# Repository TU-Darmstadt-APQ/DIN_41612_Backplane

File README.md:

# 19″ IEC 60603-2 (DIN 41612) Backplane
This repository contains the [KiCad](https://www.kicad.org/) schematics and design files for a 19″ backplane designed according to [IEEE 1101.1-1998](https://ieeexplore.ieee.org/document/741932) to mount the laser electronics in the [Eurocard](https://en.wikipedia.org/wiki/Eurocard_(printed_circuit_board)) form factor developed by APQ. See [below](#introduction) for a list of compatible devices. The design files can be found on the [releases](../../releases) page.

## Contents
- [Introduction](#introduction)
- [Datasheet](#datasheet)
- [Installation](#installation)
- [Design Files](#design-files)
- [Related Repositories](#related-repositories)
- [Versioning](#versioning)
- [License](#license)

## Introduction
This repository contains the schematics for the APQ 19″ sub-rack backplanes to mount electronics within a 19″ rack. The backplanes use several [IEC 60603-2](https://en.wikipedia.org/wiki/DIN_41612) C64AC connectors that can be configured to mount several different types of [Eurocard](https://en.wikipedia.org/wiki/Eurocard_(printed_circuit_board)) devices used by this group.  There is space for up to 6 connectors mountable in different positions to accommodate both the [Fischer Elektronik HB ME 14](https://www.fischerelektronik.com/web_fischer/en_GB/cases/N06.011/19%22%20insert%20modules/$catalogue/fischerData/PR/HBME14_/index.xhtml) and the [Fischer Elektronik TFP 3 14](https://www.fischerelektronik.com/web_fischer/en_GB/cases/N06.05/Part%20front%20panels/$catalogue/fischerData/PR/TFP14/index.xhtml) system.

Compatible devices can be found here:
- [Digital Controller for Laser Frequency Stabilization](https://github.com/TU-Darmstadt-APQ/RedPitaya-Lockbox) (RedPitaya-Lockbox)
- [Digital Controller for Laser Intensity Stabilization](https://github.com/TU-Darmstadt-APQ/RedPitaya-IntStab) (RedPitaya-IntStab)
- [Ultra Low Noise Diode Laser Driver](https://github.com/TU-Darmstadt-APQ/DgDrive) (DgDrive)
- [Phase-Frequency Detector](https://github.com/TU-Darmstadt-APQ/phase-frequency_detector)
- [Modulation Transfer Spectroscopy (MTS) Module](https://github.com/TU-Darmstadt-APQ/MTS_module)
- [Multi-purpose OpAmp Circuit Board](https://github.com/TU-Darmstadt-APQ/Multi-purpose_OpAmp_Circuit)
- [PDH Module](https://github.com/TU-Darmstadt-APQ/PDH-module)

## Datasheet
There is a datasheet available that lists the most important electrical and mechanical specifications. The latest version can be found [here](../../releases/latest/download/datasheet.pdf). Older version can be found attached to the respective [release](../../releases).

## Installation
The backplane is designed to be mounted inside a 19″ sub-rack chassis.  The most common systems used in this group are the [Schroff EuropacPRO](https://schroff.nvent.com/de-de/products/enc24563-142) and the [Fischer Elektronik BGT 384 180](https://www.fischerelektronik.de/web_fischer/en_GB/cases/N05.1/19%22%20subracks/$catalogue/fischerData/PR/BGT384_180/search.xhtml). Additionally a power supply must be provided. Typically, a rack mountable DC power supply like an [HP 6632B](https://www.keysight.com/us/en/product/6632B/100-watt-system-power-supply-20v-5a.html) is used for each rail.

### Required components and tools
- [ ] Torque screwdriver of size TX8, set to 0.3 Nm
- [ ] 1.3 mm screwdriver for hexagonal socket screws
- [ ] [3 U](https://en.wikipedia.org/wiki/Rack_unit) 19″ sub-rack chassis
  - [Schroff EuropacPRO](https://schroff.nvent.com/de-de/products/enc24563-142) or
  - [Fischer Elektronik BGT 384 180](https://www.fischerelektronik.de/web_fischer/en_GB/cases/N05.1/19%22%20subracks/$catalogue/fischerData/PR/BGT384_180/search.xhtml)) and the following accessories:
    - 2x [Fischer Elektronik IST 84](https://www.fischerelektronik.de/web_fischer/en_GB/cases/N05.2/Accessories%20for%2019%22%20subracks/$catalogue/fischerData/PG/BGT_IST84/search.xhtml) 3 mm isolation strips. These go between the chassis and the backplane.
    - 1x [Fischer Elektronik BGT 384/2](https://www.fischerelektronik.de/web_fischer/en_GB/cases/N06.09/Mounting%20accessories/$catalogue/fischerData/PR/BGT384_2M2.5/index.xhtml) M2.5 mounting strips. A package contains for strips, two for each side of the chassis.
    - 6x [Fischer Elektronik FSC 160](https://www.fischerelektronik.de/web_fischer/en_GB/cases/N05.2/Accessories%20for%2019%22%20subracks/$catalogue/fischerData/PR/FSC160/index.xhtml), one for each module installed.
    - 1x optional [Fischer Elektronik AB211](https://www.fischerelektronik.com/web_fischer/en_GB/cases/N05.2/Accessories%20for%2019%22%20subracks/$catalogue/fischerData/PR/AB211/search.xhtml) cover panel. These can be made of mild steel on special order for additional magnetic shielding compared to aluminium.
- [ ] Power supply with ±15 V outputs
- [ ] Power cable with a  [MSTB 2,5 HC/ 3-ST-5,08](https://www.phoenixcontact.com/en-us/products/pcb-plug-mstb-25-hc-3-st-508-1911978). See [power cable assembly](#power-cable-assembly) below for details.
- [ ] Up to 6  female straight [IEC 60603-2](https://en.wikipedia.org/wiki/DIN_41612)  C64AC connectors depending on the number of devices to be installed. Use class 1 or 2 connectors for better longevity. Examples are [ept 304-40054-01](https://www.ept-connectors.com/index.php?304-40054-01_en) via [Farnell](https://de.farnell.com/ept/304-40054-01/steckv-din-41612-buchsenleist/dp/2758954?st=304-40054-01) or [Harting 09032646824](https://b2b.harting.com/ebusiness/de/DIN-Signal-C064FS-29C1-2/09032646824) via [RS](https://de.rs-online.com/web/p/din-41612-steckverbinder/9235025) or [Mouser](https://eu.mouser.com/ProductDetail/HARTING/09032646824?qs=gIpPgrDBK%2FjuvkAKv%252BIFBQ%3D%3D).
- [ ] 8x M2.5x8 DIN 914 / ISO 4027 set screws to fasten the  [Fischer Elektronik BGT 384/2](https://www.fischerelektronik.de/web_fischer/en_GB/cases/N06.09/Mounting%20accessories/$catalogue/fischerData/PR/BGT384_2M2.5/index.xhtml) mounting strips
 - [ ] 10x M2.5x10 ISO 14583 TX8 screws
 - [ ] 10x M2.5 DIN 125-A / ISO 7089 plain washers

### Installation steps
> [!IMPORTANT]
> Use a torque screwdriver (0.3 Nm) to tighten the screws holding the PCB, otherwise the PCB might flex and damage components.

- Start by soldering in the [IEC 60603-2](https://en.wikipedia.org/wiki/DIN_41612) connectors. There are markings on the PCB that show where to install these depending on the type of device enclosure used. Devices built around [Fischer Elektronik HB ME 14](https://www.fischerelektronik.com/web_fischer/en_GB/cases/N06.011/19%22%20insert%20modules/$catalogue/fischerData/PR/HBME14_/index.xhtml) and [Fischer Elektronik TFP 3 14](https://www.fischerelektronik.com/web_fischer/en_GB/cases/N06.05/Part%20front%20panels/$catalogue/fischerData/PR/TFP14/index.xhtml) are supported.
- The backplane must be fixed to the subrack assembly by 5 equidistant M2.5x10 mm TX8 screws installed in each of the top and bottom row of mounting holes. Use the torque screwdriver set to 0.3 Nm to fasten the screws. Do not use a higher torque or the PCB might flex and damage the SMD ceramic capacitors. Do also remember to put the [Fischer Elektronik IST 84](https://www.fischerelektronik.de/web_fischer/en_GB/cases/N05.2/Accessories%20for%2019%22%20subracks/$catalogue/fischerData/PG/BGT_IST84/search.xhtml) 3 mm isolation strips between the backplane and the subrack if using a Fischer rack. Similar strips come with the  [Schroff EuropacPRO](https://schroff.nvent.com/de-de/products/enc24563-142) subracks as well. Otherwise the [Eurocard](https://en.wikipedia.org/wiki/Eurocard_(printed_circuit_board)) modules will not fit.
- Once firmly installed, connect the [power cable](power-cable-assembly) to the PCB and the power supply and set the the power supply to ±15 V without any devices inserted into the sub-rack. When the power supply is turned on, two green LEDs should light up to signal that the input voltage is of correct polarity and value.
- Turn off the power supply and insert the devices.

### Power cable assembly
The board has a [MSTBA 2,5 HC/ 3-G-5,08](https://www.phoenixcontact.com/en-us/products/pcb-header-mstba-25-hc-3-g-508-1923872) header. The plug required on the cable side is a [MSTB 2,5 HC/ 3-ST-5,08](https://www.phoenixcontact.com/en-us/products/pcb-plug-mstb-25-hc-3-st-508-1911978) Do note, there is an **HC** (16 A) and a **non-HC** (12 A) variant of the connector. The **HC** variant is required to meet the specifications. Typically, the other end of the cable features 4 mm connectors like the [Stäubli LQ-4N-39](https://www.staubli.com/global/en/electrical-connectors/products/t-m-products/products-for-test-accessories/plugs-2-mm-and-4-mm/plugs-LQ-4-LM-4.html) to connect to the DC power supply.

For low currents up to 5 A per rail  (Note: This means 10 A combined on the common return rail) a [LAPP ÖLFLEX CLASSIC 115 CY 3G1,5](https://e.lapp.com/apac/p/cables-for-standard-applications/oelflex-classic-115-cy-3g1-5-1136303) shielded cable with 3 cores and 1.5 mm² wires can be used. For the full rated current a 2.5 mm² 3-core cable like a [LAPP ÖLFLEX CLASSIC 115 CY 3G2,5](https://e.lapp.com/apac/p/cables-for-standard-applications/oelflex-classic-115-cy-3g2-5-1136403) is required. The cables recommended do not have an inner sheath and are therefore lighter and more flexible than regular cables with an inner sheath. This is convenient for routing the cable inside the rack. The cables are not colour-coded, but rather use numbers printed on each of the black wires. Alternative cables that have an inner sheath are [LAPP ÖLFLEX CLASSIC 110 CY 3G2,5](https://e.lapp.com/apac/p/cables-for-standard-applications/oelflex-classic-110-cy-3g2-5-1135403)  (more rigid) and [LAPP ÖLFLEX CLASSIC 100 CY 300/500V 3G2,5](https://e.lapp.com/apac/p/cables-for-standard-applications/oelflex-classic-100-cy-300-500v-3g2-5-11356502)  (more rigid *and* colour-coded). The author does not have any affiliation with the Lapp Group and any other cable with similar specifications will work as well. The cables mentioned are meant as examples.

To assemble a cable proceed as follows to produce a cable with the dimensions shown below.

#### Backplane connector
The backplane side, using a [MSTB 2,5 HC/ 3-ST-5,08](https://www.phoenixcontact.com/en-us/products/pcb-plug-mstb-25-hc-3-st-508-1911978) connector, is straightforward:

1. Cut back the outer sheath by 5 cm and remove it.
2. Trim the braid to about 1 cm and fold it back.
3. Put shrink tube over the braid and the cut.
4. Strip the three wires using a wire stripper.
5. Twist the cores.
6. Insert the wire labeled number 1 into position 1, the green/yellow wire then goes into the center, and the black wire labeled number 2 must be inserted into position 3.

#### Power supply connectors
The 4 mm connectors for the DC power supply require more work because the common conductor needs to be spliced. The desired end result is:

- 4 connectors (red, blue, 2x black) on 15 cm wires
- 1 yellow connector on a 20 cm wire

To get there, do the following:

1. Cut back the outer sheath by 15 cm and remove it
2. Trim the braid to about 2 cm and solder an 18 cm yellow 1.5 mm² wire to it.
3. Place shrink tube over the yellow solder joint
4. Trim the center green/yellow conductor of the cabel to about 2 cm
5. Solder two 13 cm  2.5 mm² wires to it and place black shrink tube over the solder joint.
6. Place black shrink tube over the black splice of the common rail.
7. Place shrink tube over all wires.
8. Strip all five cores using a wire stripper.
9. Twist the cores.
10. Solder the 4 mm connectors to the wires. Core 1 is red, core 2 is blue, the spliced core takes the two black connectors the yellow wire soldered to the shield is connected to the yellow connector.

#### Power cable labels
Use a label maker and put a label stating the maximum current and voltage on the cable:

- `16 A/60 V max` if using an **HC** connector **and** 2.5 mm² cables
- `12 A/60 V max` if using a **non-HC** connector **or** any 1.5 mm² cables (excluding the yellow cable connected to the braid)

## Design Files
### For production
The design files required for the PCB production and assembly can be found on the [releases](../../releases) page and include the following resources:

- Schematics as a PDF
- Gerber files
- Pick & place position files
- Bill of materials as a CSV file and also as an interactive HTML version

The latest revision of those files can be found [here](../../releases/latest).

#### Variants
Several variants of the design files are provided for the user. There is a so-called *default* variant, a *HBME* variant and a *TFP* variant.

##### Default variant
The default variant does not contain any [IEC 60603-2](https://en.wikipedia.org/wiki/DIN_41612) connectors. This is the version sent to the boardhouse for assembly and it is the version that is found on new backplanes. It allows the user to customize the backplane for several different devices. Depending on the type of device used in the subrack, the [IEC 60603-2](https://en.wikipedia.org/wiki/DIN_41612) connector must be installed in a different position. This is discussed below.

##### HBME variant
This variant is an example where all slots are equipped with [IEC 60603-2](https://en.wikipedia.org/wiki/DIN_41612) connectors for devices that come in the [Fischer Elektronik HB ME 14](https://www.fischerelektronik.com/web_fischer/en_GB/cases/N06.011/19%22%20insert%20modules/$catalogue/fischerData/PR/HBME14_/index.xhtml) form factor. These are fully shielded devices that come with an enclosure.

> [!NOTE]
> It is possible to mix the [HBME](#hbme-variant) and the [TFP](#tfp-variant) variant depending on the desired setup.

##### TFP variant
The TFP variant is used for devices utilizing the [Fischer Elektronik TFP 3 14](https://www.fischerelektronik.com/web_fischer/en_GB/cases/N06.05/Part%20front%20panels/$catalogue/fischerData/PR/TFP14/index.xhtml) assembly. These device have an open frame. The design files show an example configuration that uses [IEC 60603-2](https://en.wikipedia.org/wiki/DIN_41612) connectors considering a subrack full of [TFP](https://www.fischerelektronik.com/web_fischer/en_GB/cases/N06.05/Part%20front%20panels/$catalogue/fischerData/PR/TFP14/index.xhtml) devices.

> [!NOTE]
> It is possible to mix the [HBME](#hbme-variant) and the [TFP](#tfp-variant) variant depending on the desired setup.

### For editing
To work on the [KiCad](https://www.kicad.org/) design files, a number of external libraries are needed. Those libraries show up as empty folders in the zip file, because they are not included in the release, but must be downloaded separately from the links given [below](#related-repositories). This can be avoided by checking out the whole repository using git. This way the libraries will be downloaded as well. Use the following command to clone the git repository along with the submodules  using the `--recurse-submodules` flag.
```
git clone --recurse-submodules https://github.com/TU-Darmstadt-APQ/DIN_41612_Backplane.git
```

## Related Repositories
See the following repositories for more information as these are part of the [design files](#design-files).

- [KiCad footprints](https://github.com/PatrickBaus/footprints.pretty)
- [KiCAD 3D models](https://github.com/PatrickBaus/footprints.3dshapes)
- [KiCAD schematic libraries](https://github.com/PatrickBaus/KiCad-libraries)

## Versioning
I use [SemVer](http://semver.org/) for versioning. For the versions available, see the [tags](../../tags) available for this repository.

- MAJOR versions in this context mean a breaking change to the external interface of the hardware like different connectors or functions.
- MINOR versions contain changes to the hardware that only affect the inner workings of the circuit, but otherwise the performance is unaffected.
- PATCH versions do not affect the schematics or invalidate older bill of materials. These changes may include updated components (to replace obsolete parts for example), an updated silkscreen, or fixed typos.

## License
This work is released under the CERN-OHL-W
See [https://ohwr.org/cern_ohl_w_v2.pdf](https://ohwr.org/cern_ohl_w_v2.pdf) or the included LICENSE file for more information.

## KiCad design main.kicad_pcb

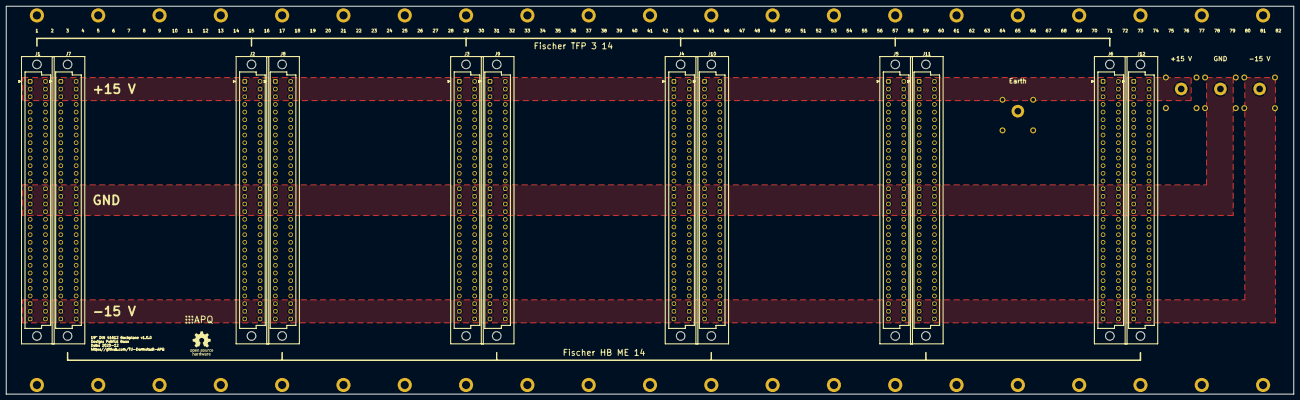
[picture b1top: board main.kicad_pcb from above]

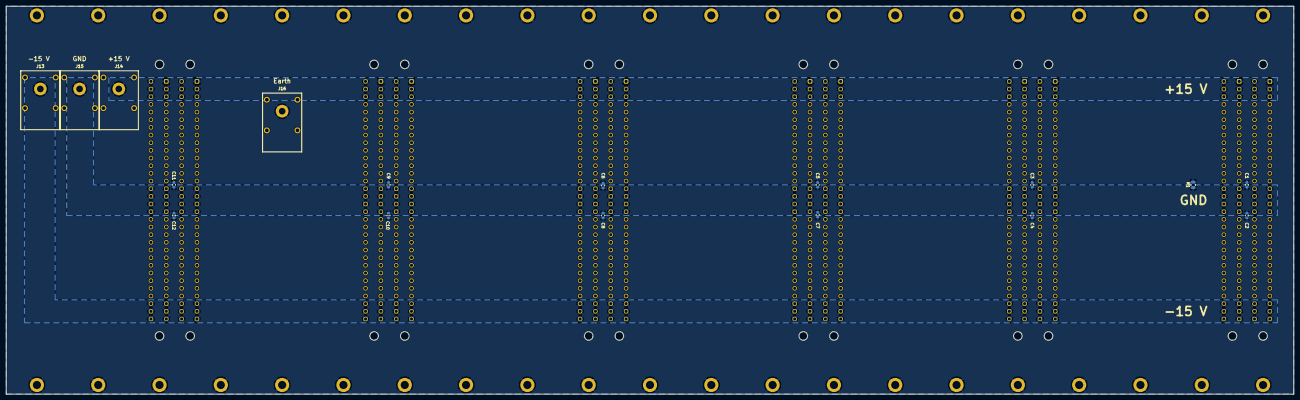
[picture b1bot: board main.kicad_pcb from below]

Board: 2 copper layers, 426.7 x 128.6 mm, 73 parts (17 on the bottom side), 4 nets, no tracks yet.

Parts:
C1, C2, C3, C4, C5, C6, C7, C8, C9, C10, C11, C12: 10n; C_0603_1608Metric
H1, H2, H3, H4, H5, H6, H7, H8, H9, H10, H11, H12, H13, H14, H15, H16, H17, H18, H19, H20, H21, H22, H23, H24, H25, H26, H27, H28, H29, H30, H31, H32, H33, H34, H35, H36, H37, H38, H39, H40, H41, H42: MountingHole; MountingHole_2.7mm_M2.5_DIN965_Pad
J1, J2, J3, J4, J5, J6, J7, J8, J9, J10, J11, J12: C64AC; DIN41612_C_2x32_Female_Vertical_THT
J13, J14, J15, J16: Conn_01x01_Female; Schuetzinger_4mm_Jack
LOGO1: Logo_APQ; APQ-Logo_small
LOGO2: Logo_Open_Hardware_Small; OSHW-Logo_7.5x8mm_SilkScreen
R1: 1M; R_0805_2012Metric

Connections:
+15V: J1.a1, J1.a2, J1.a3, J1.c1, J1.c2, J1.c3, J2.a1, J2.a2, J2.a3, J2.c1, J2.c2, J2.c3, J3.a1, J3.a2, J3.a3, J3.c1, J3.c2, J3.c3, J4.a1, J4.a2, J4.a3, J4.c1, J4.c2, J4.c3, J5.a1, J5.a2, J5.a3, J5.c1, J5.c2, J5.c3, J6.a1, J6.a2, J6.a3, J6.c1, J6.c2, J6.c3, J7.a1, J7.a2, J7.a3, J7.c1, J7.c2, J7.c3, J8.a1, J8.a2, J8.a3, J8.c1, J8.c2, J8.c3, J9.a1, J9.a2, J9.a3, J9.c1, J9.c2, J9.c3, J10.a1, J10.a2, J10.a3, J10.c1, J10.c2, J10.c3, J11.a1, J11.a2, J11.a3, J11.c1, J11.c2, J11.c3, J12.a1, J12.a2, J12.a3, J12.c1, J12.c2, J12.c3, J14.1
-15V: J1.a30, J1.a31, J1.a32, J1.c30, J1.c31, J1.c32, J2.a30, J2.a31, J2.a32, J2.c30, J2.c31, J2.c32, J3.a30, J3.a31, J3.a32, J3.c30, J3.c31, J3.c32, J4.a30, J4.a31, J4.a32, J4.c30, J4.c31, J4.c32, J5.a30, J5.a31, J5.a32, J5.c30, J5.c31, J5.c32, J6.a30, J6.a31, J6.a32, J6.c30, J6.c31, J6.c32, J7.a30, J7.a31, J7.a32, J7.c30, J7.c31, J7.c32, J8.a30, J8.a31, J8.a32, J8.c30, J8.c31, J8.c32, J9.a30, J9.a31, J9.a32, J9.c30, J9.c31, J9.c32, J10.a30, J10.a31, J10.a32, J10.c30, J10.c31, J10.c32, J11.a30, J11.a31, J11.a32, J11.c30, J11.c31, J11.c32, J12.a30, J12.a31, J12.a32, J12.c30, J12.c31, J12.c32, J13.1
Earth: C1.2, C2.2, C3.2, C4.2, C5.2, C6.2, C7.2, C8.2, C9.2, C10.2, C11.2, C12.2, H1.1, H2.1, H3.1, H4.1, H5.1, H6.1, H7.1, H8.1, H9.1, H10.1, H11.1, H12.1, H13.1, H14.1, H15.1, H16.1, H17.1, H18.1, H19.1, H20.1, H21.1, H22.1, H23.1, H24.1, H25.1, H26.1, H27.1, H28.1, H29.1, H30.1, H31.1, H32.1, H33.1, H34.1, H35.1, H36.1, H37.1, H38.1, H39.1, H40.1, H41.1, H42.1, J16.1, R1.2
GND: C1.1, C2.1, C3.1, C4.1, C5.1, C6.1, C7.1, C8.1, C9.1, C10.1, C11.1, C12.1, J1.a15, J1.a16, J1.a17, J1.a18, J1.c15, J1.c16, J1.c17, J1.c18, J2.a15, J2.a16, J2.a17, J2.a18, J2.c15, J2.c16, J2.c17, J2.c18, J3.a15, J3.a16, J3.a17, J3.a18, J3.c15, J3.c16, J3.c17, J3.c18, J4.a15, J4.a16, J4.a17, J4.a18, J4.c15, J4.c16, J4.c17, J4.c18, J5.a15, J5.a16, J5.a17, J5.a18, J5.c15, J5.c16, J5.c17, J5.c18, J6.a15, J6.a16, J6.a17, J6.a18, J6.c15, J6.c16, J6.c17, J6.c18, J7.a15, J7.a16, J7.a17, J7.a18, J7.c15, J7.c16, J7.c17, J7.c18, J8.a15, J8.a16, J8.a17, J8.a18, J8.c15, J8.c16, J8.c17, J8.c18, J9.a15, J9.a16, J9.a17, J9.a18, J9.c15, J9.c16, J9.c17, J9.c18, J10.a15, J10.a16, J10.a17, J10.a18, J10.c15, J10.c16, J10.c17, J10.c18, J11.a15, J11.a16, J11.a17, J11.a18, J11.c15, J11.c16, J11.c17, J11.c18, J12.a15, J12.a16, J12.a17, J12.a18, J12.c15, J12.c16, J12.c17, J12.c18, J15.1, R1.1

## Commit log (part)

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2023-09-26 Updated .gitignore for KiCAD 7
2023-09-26 Add LTSpice simulation
2023-10-25 Add git submodules to dependabot
2023-10-27 [gha] Bump PatrickBaus/latex-action from 0.0.14 to 0.0.15
    Bumps [PatrickBaus/latex-action](https://github.com/patrickbaus/latex-action) from 0.0.14 to 0.0.15.
    - [Release notes](https://github.com/patrickbaus/latex-action/releases)
    - [Commits](https://github.com/patrickbaus/latex-action/compare/0.0.14...0.0.15)
    ---
    updated-dependencies:
    - dependency-name: PatrickBaus/latex-action
2023-10-27 Fix artifact path
2023-10-27 Remove duplicate entry
2023-10-27 Remove unused docker file check from dependabot
2023-10-27 More filename fixes
2023-10-27 Only produce the gerber files for the default variant
2023-10-27 Reworked readme
2023-10-27 Configure config file
2023-11-03 Bump libraries from `607f789` to `3a2eb44`
    Bumps [libraries](https://github.com/PatrickBaus/KiCad-libraries) from `607f789` to `3a2eb44`.
    - [Commits](https://github.com/PatrickBaus/KiCad-libraries/compare/607f789a00c13ced4b12bf1024043f0bc2a5289f...3a2eb443a3fc19700c366d62fc294e66c2c94969)
    ---
    updated-dependencies:
    - dependency-name: libraries
    dependency-type: direct:production
2023-11-05 Add missing pdf extension
2023-11-14 Slightly updated datasheet to change from worst case calculations to monto-carlo simulations Added monte-carlo simulation scripts
2023-11-19 Updated readme with assembly instructions
2023-11-19 Added Ferrite beads at the board input Moved power connector silkscreen labels Added TODO list for v.2.1.0
2023-11-20 Replace negative rail NMOS with SQJQ160E to reduce the on resistance
2023-11-20 Consolidated BOM
2023-11-20 Updated board dimensions and location of connectors to match IEEE 1101.1-1991 Added markings for the mounting screws
2023-11-21 Bump footprints.pretty from `2062bdf` to `868196a`
    Bumps [footprints.pretty](https://github.com/PatrickBaus/footprints.pretty) from `2062bdf` to `868196a`.
    - [Commits](https://github.com/PatrickBaus/footprints.pretty/compare/2062bdf2f8beb043fa973c10f4aa42d4773b8c52...868196ac1af2e11168d2323acc2cf90035e7c814)
    ---
    updated-dependencies:
    - dependency-name: footprints.pretty
    dependency-type: direct:production
2023-11-21 Reduced datasheet absolute maximum voltage to ±48 V, because the TVS diodes start conducting considerably at 48 V
2023-11-21 Added test points
2023-11-21 Updated to 2.1.0
2023-11-21 Increased copper surface around hot elements Increased number of thermal vias Updated simulation to 16 A
2023-11-22 Updated QR code to point to https://github.com/TU-Darmstadt-APQ/DIN_41612_Backplane
2023-11-23 Added citation file
2023-11-23 Updated citation
2023-11-23 More citation updates
2023-11-24 Updated libs
2023-11-27 Fixed typo
2023-11-30 Bump footprints.3dshapes from `b44d94e` to `8369024`
    Bumps [footprints.3dshapes](https://github.com/PatrickBaus/footprints.3dshapes) from `b44d94e` to `8369024`.
    - [Commits](https://github.com/PatrickBaus/footprints.3dshapes/compare/b44d94e43694ceced7830d69e0519fdf0ff3c646...83690243c05aaf1695bed75f20cff05fe69fca7a)
    ---
    updated-dependencies:
    - dependency-name: footprints.3dshapes
    dependency-type: direct:production
2023-12-01 Moved rear cover to mechanical/
2023-12-01 Refactored back bover
2023-12-02 Renamed root files to from main to backplane
2023-12-04 Bump libraries from `fdcfc3f` to `50896b9`
    Bumps [libraries](https://github.com/PatrickBaus/KiCad-libraries) from `fdcfc3f` to `50896b9`.
    - [Commits](https://github.com/PatrickBaus/KiCad-libraries/compare/fdcfc3f250463fceab225ee3a982e03f9067a0d6...50896b91e8f923cd095306b51fce827216ea2790)
    ---
    updated-dependencies:
    - dependency-name: libraries
    dependency-type: direct:production
2023-12-05 Fixed footprint of Q3 and Q4
2023-12-08 Rotated screw symbols in the upper row Added screw descriptor to the silkscreen
2023-12-12 Updated libraries Removed thermal jumpers apart from one, because they are not needed
2023-12-12 Added KiCost script
2023-12-12 Updaed libs
2023-12-12 Mirrored 'Chassis' silkscreen of the Quick-connect connector
2023-12-15 [gha] Bump actions/upload-artifact from 3 to 4
    Bumps [actions/upload-artifact](https://github.com/actions/upload-artifact) from 3 to 4.
    - [Release notes](https://github.com/actions/upload-artifact/releases)
    - [Commits](https://github.com/actions/upload-artifact/compare/v3...v4)
    ---
    updated-dependencies:
    - dependency-name: actions/upload-artifact
2023-12-19 started adding holes
2023-12-19 All holes added
2024-01-02 Replaced constant current diode with KiCad device available as of v7.0.10 Updated LM5067 3D model
2024-01-09 Added more silkscreen clearance for the label of Q3 and Q4
2024-01-09 Updated CI workflow Added test for the correct git tag Updated footprint lib
2024-01-12 Updated power MOSFET PNs to match Mouser
2024-01-15 Replaced Vishay SQJQ160E with official KiCad symbol
2024-01-21 Replaced 4mm connector with latest version from https://gitlab.com/kicad/libraries/kicad-footprints/-/merge_requests/3413
2024-01-22 Fixed DRC errors Cleaned up arrow symbols Moved the power connect 25 mil to left to fix the overlapping silkscreen
2024-01-22 Improved thermal coupling of the current shunt R3
2024-01-24 Bump libraries from `2f1f39a` to `b3c5738`
    Bumps [libraries](https://github.com/PatrickBaus/KiCad-libraries) from `2f1f39a` to `b3c5738`.
    - [Commits](https://github.com/PatrickBaus/KiCad-libraries/compare/2f1f39a8283e49195b706badf4707524f394470f...b3c5738d93f36102fc3b563cb1834f994a797ebd)
    ---
    updated-dependencies:
    - dependency-name: libraries
    dependency-type: direct:production
2024-02-06 Added maximum torque information to readme
2024-02-15 Reduce retention time of artifacts
2024-03-04 Bump libraries from `fc80998` to `9087a43`
    Bumps [libraries](https://github.com/PatrickBaus/KiCad-libraries) from `fc80998` to `9087a43`.
    - [Commits](https://github.com/PatrickBaus/KiCad-libraries/compare/fc80998627a071d32dd6bf68f49bdddbbc4930bb...9087a430f879cbfa6749edcfa81bc47a02f8b949)
    ---
    updated-dependencies:
    - dependency-name: libraries
    dependency-type: direct:production
2024-03-16 Updated to KiCad 8
2024-03-18 Bump libraries from `9087a43` to `57262d7`
    Bumps [libraries](https://github.com/PatrickBaus/KiCad-libraries) from `9087a43` to `57262d7`.
    - [Commits](https://github.com/PatrickBaus/KiCad-libraries/compare/9087a430f879cbfa6749edcfa81bc47a02f8b949...57262d720a83fcb0ac734ab948d50d9c8d024147)
    ---
    updated-dependencies:
    - dependency-name: libraries
    dependency-type: direct:production
2024-03-30 Chaged to CI dev branch
2024-03-30 More DRC fixes
2024-03-31 Update CI to KiCad 8 (#24)
    * Updated CI to KiCad 8
2024-04-01 Bump libraries from `57262d7` to `b8f384f`
    Bumps [libraries](https://github.com/PatrickBaus/KiCad-libraries) from `57262d7` to `b8f384f`.
    - [Commits](https://github.com/PatrickBaus/KiCad-libraries/compare/57262d720a83fcb0ac734ab948d50d9c8d024147...b8f384f78333fe525837db93492238eb43cf1dca)
    ---
    updated-dependencies:
    - dependency-name: libraries
    dependency-type: direct:production
2024-04-14 Updated libraries
2024-04-16 Updated changelog
2024-04-29 Update kibot config to new erc config
2024-04-29 CI: Check out submodules before testing
2024-04-29 Partially reverted 0f44693
2024-04-29 Bump footprints.pretty from `14a956a` to `0b98113`
    Bumps [footprints.pretty](https://github.com/PatrickBaus/footprints.pretty) from `14a956a` to `0b98113`.
    - [Commits](https://github.com/PatrickBaus/footprints.pretty/compare/14a956adad21c401ba564977f26300822d56e9d1...0b98113018f286dab911dbd6fe602511ebc8c964)
    ---
    updated-dependencies:
    - dependency-name: footprints.pretty
    dependency-type: direct:production
2024-05-08 Update Python pre-commit hooks
2024-05-08 Updated silkscreen labelmaker instructions
2024-05-22 --- updated-dependencies: - dependency-name: footprints.pretty dependency-type: direct:production ...
2024-06-03 Added TARIC number
2024-06-17 Bump libraries from `ff94194` to `80d58ef`
    Bumps [libraries](https://github.com/PatrickBaus/KiCad-libraries) from `ff94194` to `80d58ef`.
    - [Commits](https://github.com/PatrickBaus/KiCad-libraries/compare/ff94194adcf619829e0e65c1c6c080f5b8c78d84...80d58efa29fc28aa49b090516bd5b7168ac740c8)
    ---
    updated-dependencies:
    - dependency-name: libraries
    dependency-type: direct:production
2025-02-13 Added wire core numbers to the text describing the connector colours (#34)
2025-04-07 Fixed typo (#35)
2025-04-19 Fixed spelling errors in code comments
2025-08-06 [gha] Bump actions/download-artifact from 4 to 5 (#38)
    Bumps [actions/download-artifact](https://github.com/actions/download-artifact) from 4 to 5.
    - [Release notes](https://github.com/actions/download-artifact/releases)
    - [Commits](https://github.com/actions/download-artifact/compare/v4...v5)
    ---
    updated-dependencies:
    - dependency-name: actions/download-artifact
2025-09-22 [gha] Bump wtfjoke/setup-tectonic from 3 to 4
    Bumps [wtfjoke/setup-tectonic](https://github.com/wtfjoke/setup-tectonic) from 3 to 4.
    - [Release notes](https://github.com/wtfjoke/setup-tectonic/releases)
    - [Commits](https://github.com/wtfjoke/setup-tectonic/compare/v3...v4)
    ---
    updated-dependencies:
    - dependency-name: wtfjoke/setup-tectonic
2025-10-27 [gha] Bump actions/download-artifact from 5 to 6 (#41)
    Bumps [actions/download-artifact](https://github.com/actions/download-artifact) from 5 to 6.
    - [Release notes](https://github.com/actions/download-artifact/releases)
    - [Commits](https://github.com/actions/download-artifact/compare/v5...v6)
    ---
    updated-dependencies:
    - dependency-name: actions/download-artifact
2025-10-27 [gha] Bump wtfjoke/setup-tectonic from 3 to 4 (#40)
    Bumps [wtfjoke/setup-tectonic](https://github.com/wtfjoke/setup-tectonic) from 3 to 4.
    - [Release notes](https://github.com/wtfjoke/setup-tectonic/releases)
    - [Commits](https://github.com/wtfjoke/setup-tectonic/compare/v3...v4)
    ---
    updated-dependencies:
    - dependency-name: wtfjoke/setup-tectonic
2025-11-26 Bump libraries from `80d58ef` to `ba5563d`
    Bumps [libraries](https://github.com/PatrickBaus/KiCad-libraries) from `80d58ef` to `ba5563d`.
    - [Commits](https://github.com/PatrickBaus/KiCad-libraries/compare/80d58efa29fc28aa49b090516bd5b7168ac740c8...ba5563d66c23dea06d561adcb039ddac5a03efdf)
    ---
    updated-dependencies:
    - dependency-name: libraries
    dependency-version: ba5563d66c23dea06d561adcb039ddac5a03efdf
2025-12-15 [gha] Bump actions/upload-artifact from 5 to 6
    Bumps [actions/upload-artifact](https://github.com/actions/upload-artifact) from 5 to 6.
    - [Release notes](https://github.com/actions/upload-artifact/releases)
    - [Commits](https://github.com/actions/upload-artifact/compare/v5...v6)
    ---
    updated-dependencies:
    - dependency-name: actions/upload-artifact
2025-12-15 [gha] Bump actions/upload-artifact from 5 to 6 (#46)
    Bumps [actions/upload-artifact](https://github.com/actions/upload-artifact) from 5 to 6.
    - [Release notes](https://github.com/actions/upload-artifact/releases)
    - [Commits](https://github.com/actions/upload-artifact/compare/v5...v6)
    ---
    updated-dependencies:
    - dependency-name: actions/upload-artifact
2026-02-09 Bump libraries from `d79317d` to `4179135`
    Bumps [libraries](https://github.com/PatrickBaus/KiCad-libraries) from `d79317d` to `4179135`.
    - [Commits](https://github.com/PatrickBaus/KiCad-libraries/compare/d79317d926704a58090a36fac06bfafa731a048b...41791358010d2de5d2401e25bd30de257630acf6)
    ---
    updated-dependencies:
    - dependency-name: libraries
    dependency-version: 41791358010d2de5d2401e25bd30de257630acf6
2026-02-27 [gha] Bump actions/download-artifact from 7 to 8
    Bumps [actions/download-artifact](https://github.com/actions/download-artifact) from 7 to 8.
    - [Release notes](https://github.com/actions/download-artifact/releases)
    - [Commits](https://github.com/actions/download-artifact/compare/v7...v8)
    ---
    updated-dependencies:
    - dependency-name: actions/download-artifact

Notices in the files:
main.kicad_pcb:
Copyright (©) 2020, Patrick Baus
Licensed under CERN OHL v.1.2
